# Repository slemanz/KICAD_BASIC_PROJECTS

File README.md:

# KICAD BASIC PROJECTS

Placeholder first commit.

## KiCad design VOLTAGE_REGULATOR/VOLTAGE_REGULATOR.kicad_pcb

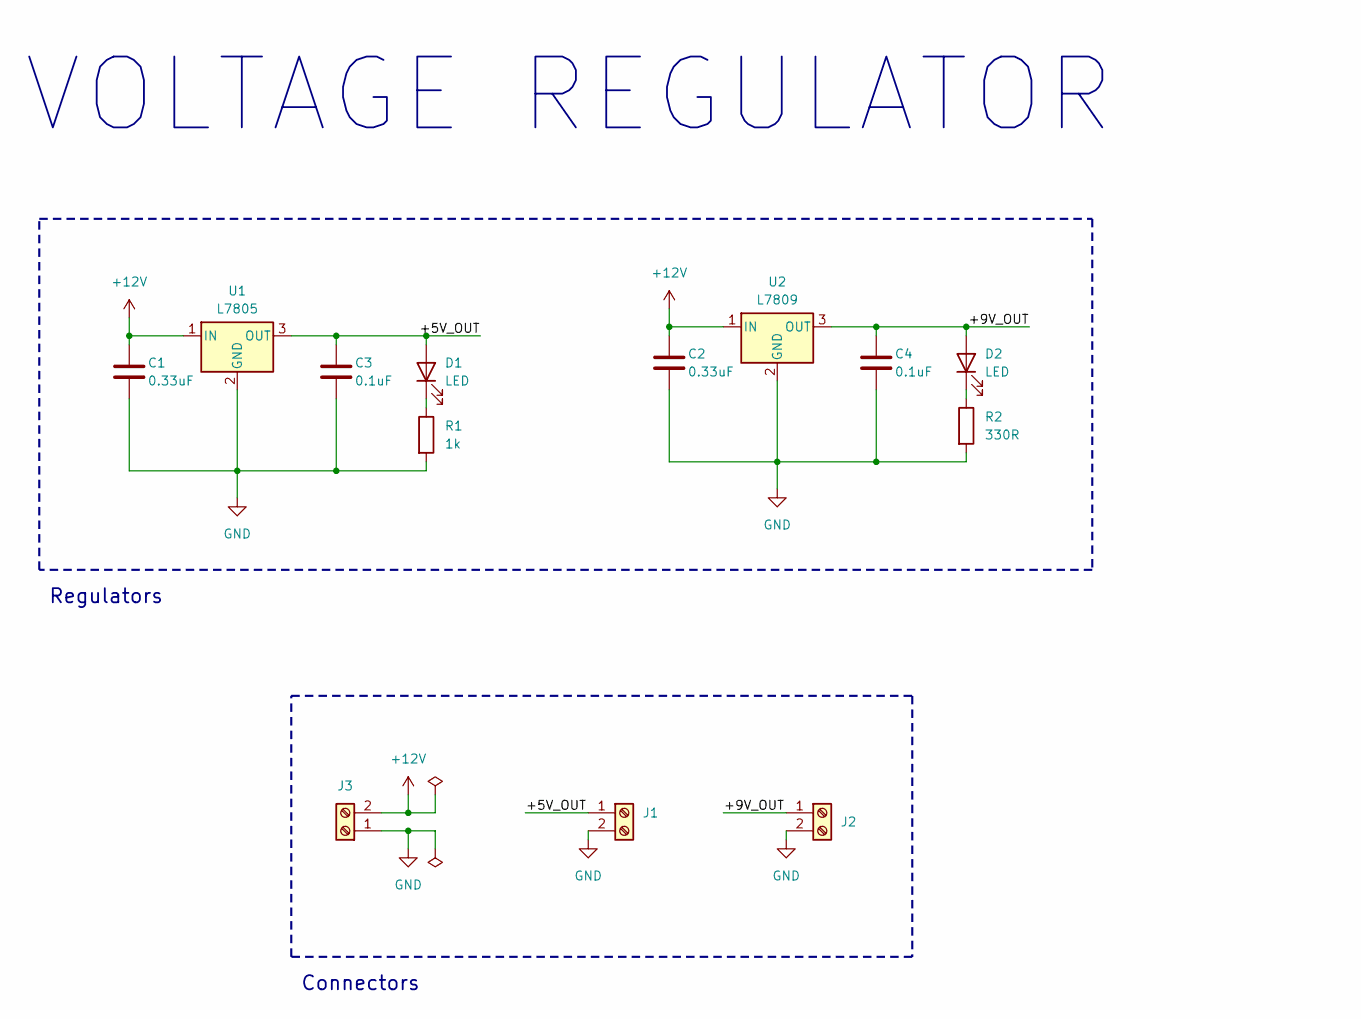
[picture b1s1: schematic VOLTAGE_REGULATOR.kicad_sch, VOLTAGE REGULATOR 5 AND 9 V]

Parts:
C1, C2: 0.33uF; C_Disc_D4.7mm_W2.5mm_P5.00mm
C3, C4: 0.1uF; C_Disc_D3.0mm_W2.0mm_P2.50mm
D1, D2: LED; LED_D4.0mm
J1, J2, J3: Screw_Terminal_01x02; TerminalBlock_Phoenix_MKDS-1,5-2-5.08_1x02_P5.08mm_Horizont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
R1: 1k; R_Axial_DIN0207_L6.3mm_D2.5mm_P7.62mm_Horizontal
R2: 330R; R_Axial_DIN0207_L6.3mm_D2.5mm_P7.62mm_Horizontal
U1: L7805; TO-220-3_Vertical
U2: L7809; TO-220-3_Vertical

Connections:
+12V: C1.1, C2.1, J3.2, U1.1 (IN), U2.1 (IN)
/+5V_OUT: C3.1, D1.2 (A), J1.1, U1.3 (OUT)
/+9V_OUT: C4.1, D2.2 (A), J2.1, U2.3 (OUT)
GND: C1.2, C2.2, C3.2, C4.2, J1.2, J2.2, J3.1, R1.2, R2.2, U1.2 (GND), U2.2 (GND)
unnamed: D1.1 (K), R1.1
unnamed: D2.1 (K), R2.1

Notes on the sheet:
VOLTAGE REGULATOR
Connectors
Regulators

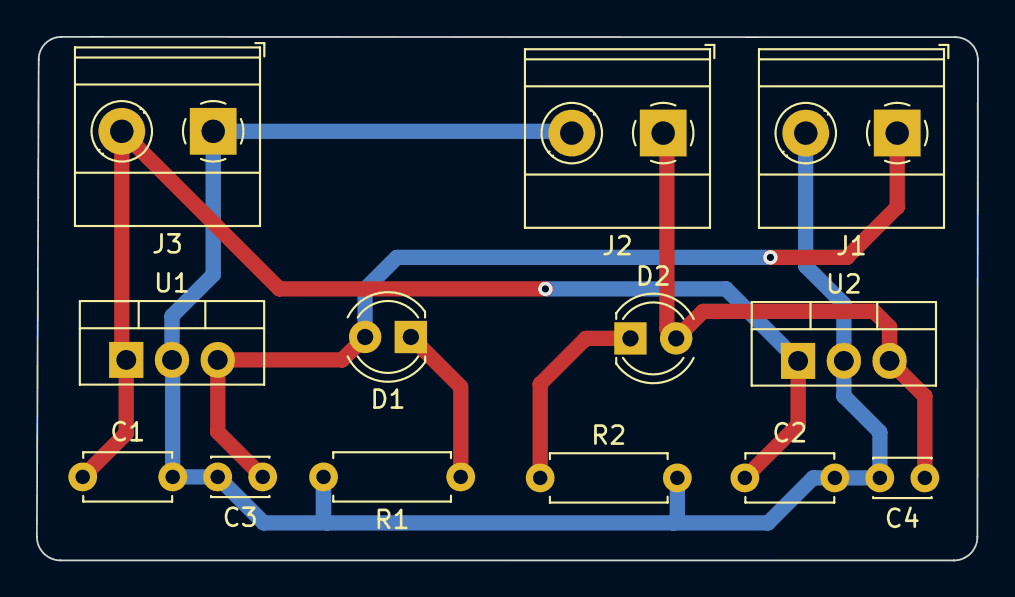
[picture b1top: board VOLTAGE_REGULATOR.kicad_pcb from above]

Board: 2 copper layers, 52.3 x 29.1 mm, 13 parts (0 on the bottom side), 6 nets.

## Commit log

2023-12-05 project (created): add first readme file
2023-12-05 project(created): create motor controller project
2023-12-26 voltage reg(project): create project
2023-12-26 voltage regulator(project): change schematic
2023-12-27 voltage regulator(project): add footprints
2024-01-09 project(feat): update pcb
2024-01-10 voltage regulator: place components
2024-01-10 remove some files
2024-01-12 route pcb main connections
2024-01-13 voltage regulator: add fill zones
